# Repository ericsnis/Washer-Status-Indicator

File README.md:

# Washer Status Indicator
Washing Machine status indicator using a ESP32-C3 based Adafruit QT Py

## Features

- Simple LED indicator for at a glance washing machine and clothes dryer status.
  - Green LED for "OFF / Ready"
  - Red LED for "ON/ In Use"
  - Could be used to indicate status of other things.
- Open source hardware
- Software uses [PubSubClient](https://pubsubclient.knolleary.net/) to communicate with MQTT server
  - Uses [OpenHab](https://www.openhab.org/) home automation sever for source of MQTT data.
    - Requires MQTT server such as [Mosquitto](https://mosquitto.org/).
	  - [Basic directions](https://community.openhab.org/t/oh3-mqtt-setup-and-configuration) for Mosquitto and OpenHab
    - Follow directions for configuring [MQTT binding](https://www.openhab.org/addons/bindings/mqtt/).
  - Could be used with other MQTT sources like [Home Assistant](https://www.home-assistant.io/).

## Boards
The schematic folder contains the board and schematic files in Eagle format
- Designs for 1206 SMT LEDs and resistors or through hole components

## Code
The code folder contains the program code to compile and upload to the ESP32
- Use [Platform.io](https://docs.platformio.org/en/latest/integration/ide/vscode.html) installed on [Visual Studio Code](https://code.visualstudio.com/) AKA: VSCode to compile and upload.
- Open the code folder in VSCode then compile, PlatformIO should download any dependencies.

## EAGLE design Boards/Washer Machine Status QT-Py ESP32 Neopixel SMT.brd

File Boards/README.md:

# Boards
 The schematic folder contains the board and schematic files in Eagle format

## Files for surface mount (SMT) boards
- _Washer Machine Status QT-Py ESP32 Neopixel SMT.brd_ - Surface mount board file
- _Washer Machine Status QT-Py ESP32 Neopixel SMT.sch_ - Surface mount schematic file

## Files for through hole component boards
- _Washer Machine Status QT-Py ESP32 Neopixel THT.brd_ - Through hole component board file
- _Washer Machine Status QT-Py ESP32 Neopixel THT.sch_ - Through hole component schematic file

**You need _both_ the .brd and .sch files to open the board in Eagle.**

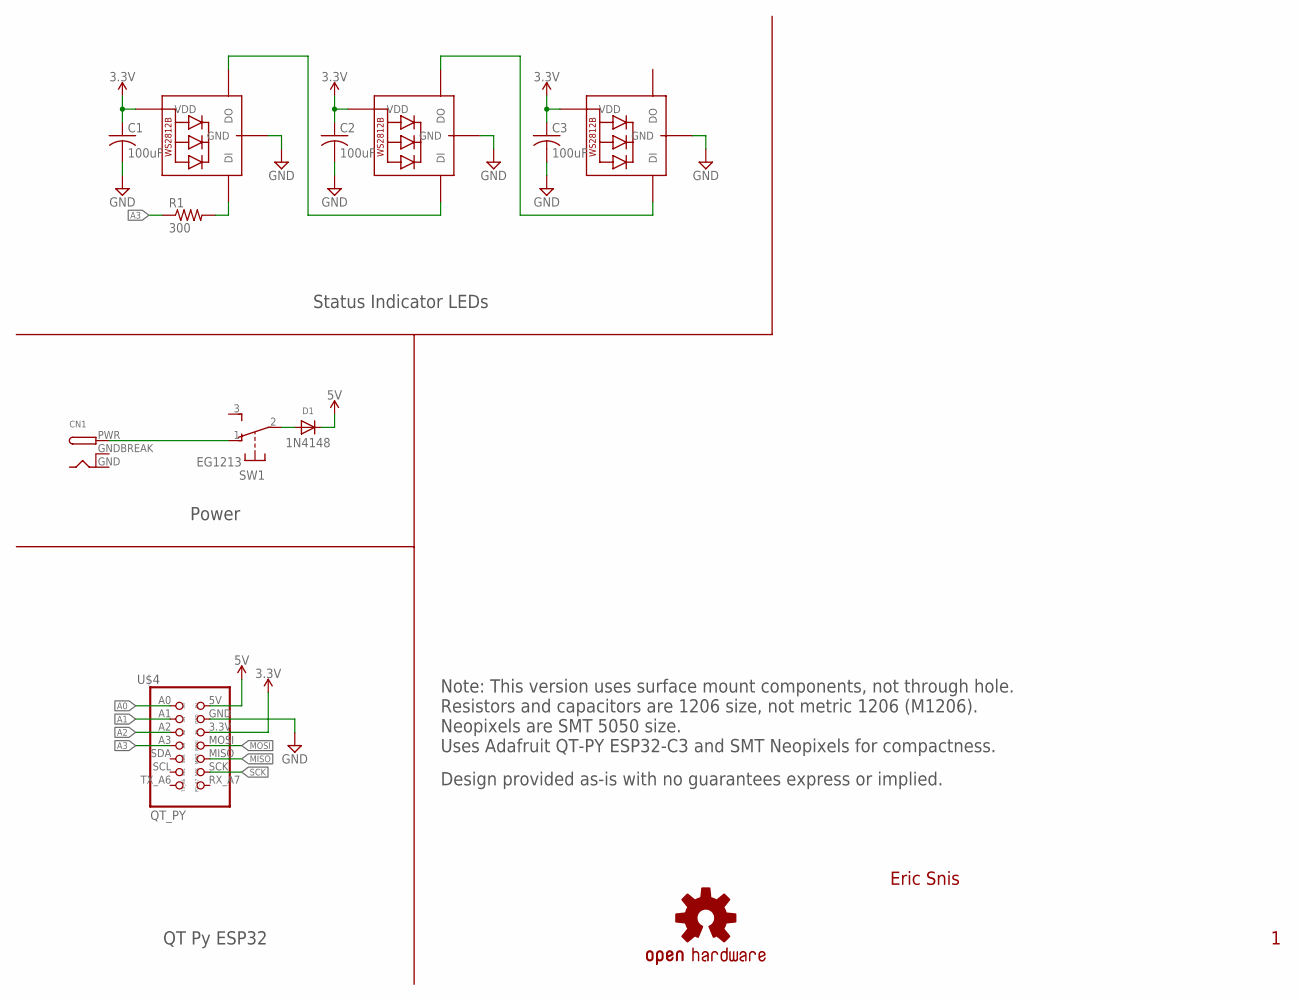
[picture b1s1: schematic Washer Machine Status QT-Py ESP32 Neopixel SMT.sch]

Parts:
C1, C2, C3: 100uF; C1206
CN1: DCBARRELPTH; DCJACK_2MM_PTH
D1: 1N4148; SOD-123FL
LED1, LED2, LED3: WS2812B5050; WS2812B
LOGO2: OSHW-LOGOMINI; OSHW-LOGO-MINI
R1: 300; R1206
SW: EG1213
U$4: QT_PY

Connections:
3.3V: C1.1, C2.1, C3.1, LED1.1-VDD (VDD), LED2.1-VDD (VDD), LED3.1-VDD (VDD), U$4.3.3V (3V)
5V: D1.C, U$4.5V
A0: U$4.A0
A1: U$4.A1
A2: U$4.A2
A3: R1.1, U$4.A3
GND: C1.2, C2.2, C3.2, CN1.GND, LED1.3-GND (GND), LED2.3-GND (GND), LED3.3-GND (GND), U$4.GND
GNDBREAK: CN1.GNDBREAK
MISO: U$4.MISO
MOSI: U$4.MOSI
unnamed: CN1.PWR, SW.1 (O)
unnamed: LED1.2-DOUT (DO), LED2.4-DIN (DI)
unnamed: LED1.4-DIN (DI), R1.2
unnamed: LED2.2-DOUT (DO), LED3.4-DIN (DI)
unnamed: D1.A, SW.2
SCK: U$4.SCK

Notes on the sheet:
Status Indicator LEDs
Power
QT Py ESP32
Note: This version uses surface mount components, not through hole. Resistors and capacitors are 1206 size, not metric 1206 (M1206). Neopixels are SMT 5050 size. Uses Adafruit QT-PY ESP32-C3 and SMT Neopixels for compactness.
Design provided as-is with no guarantees express or implied.

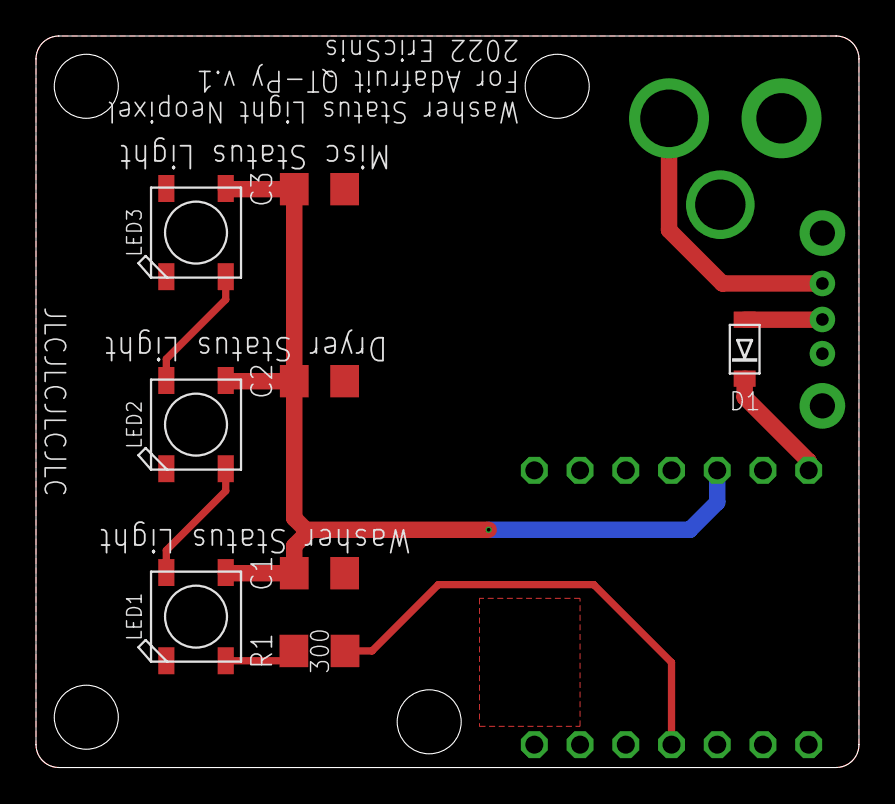
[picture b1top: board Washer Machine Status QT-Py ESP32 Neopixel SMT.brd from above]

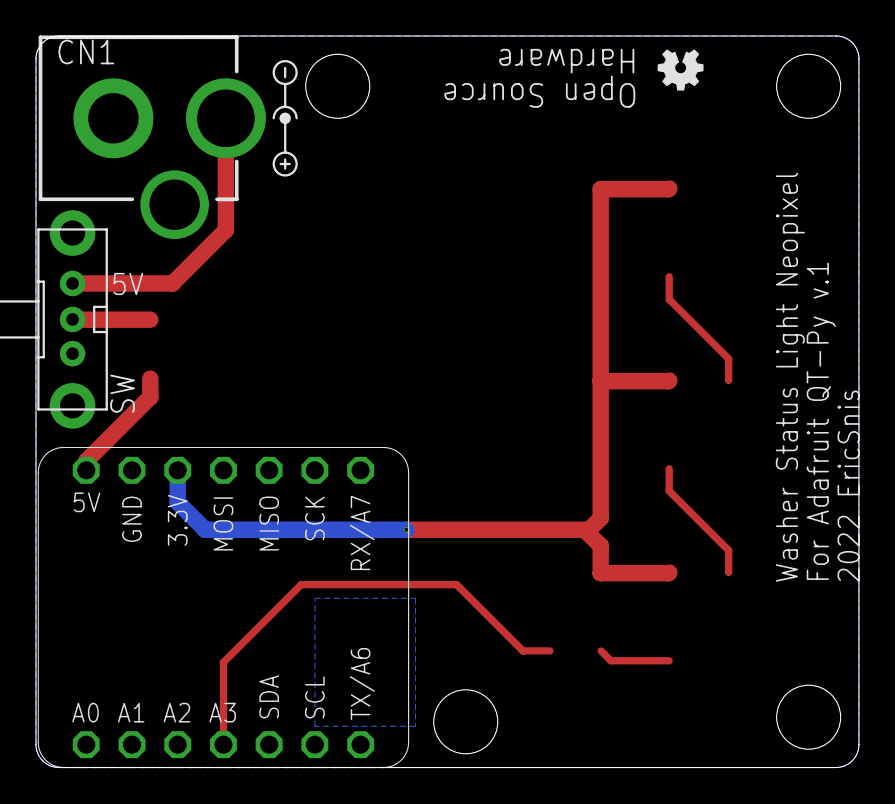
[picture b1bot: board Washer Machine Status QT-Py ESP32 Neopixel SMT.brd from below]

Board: 2 copper layers, 45.7 x 40.6 mm, 13 parts (5 on the bottom side), 9 nets.

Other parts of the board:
U$1: CENTER-POS-SMALL

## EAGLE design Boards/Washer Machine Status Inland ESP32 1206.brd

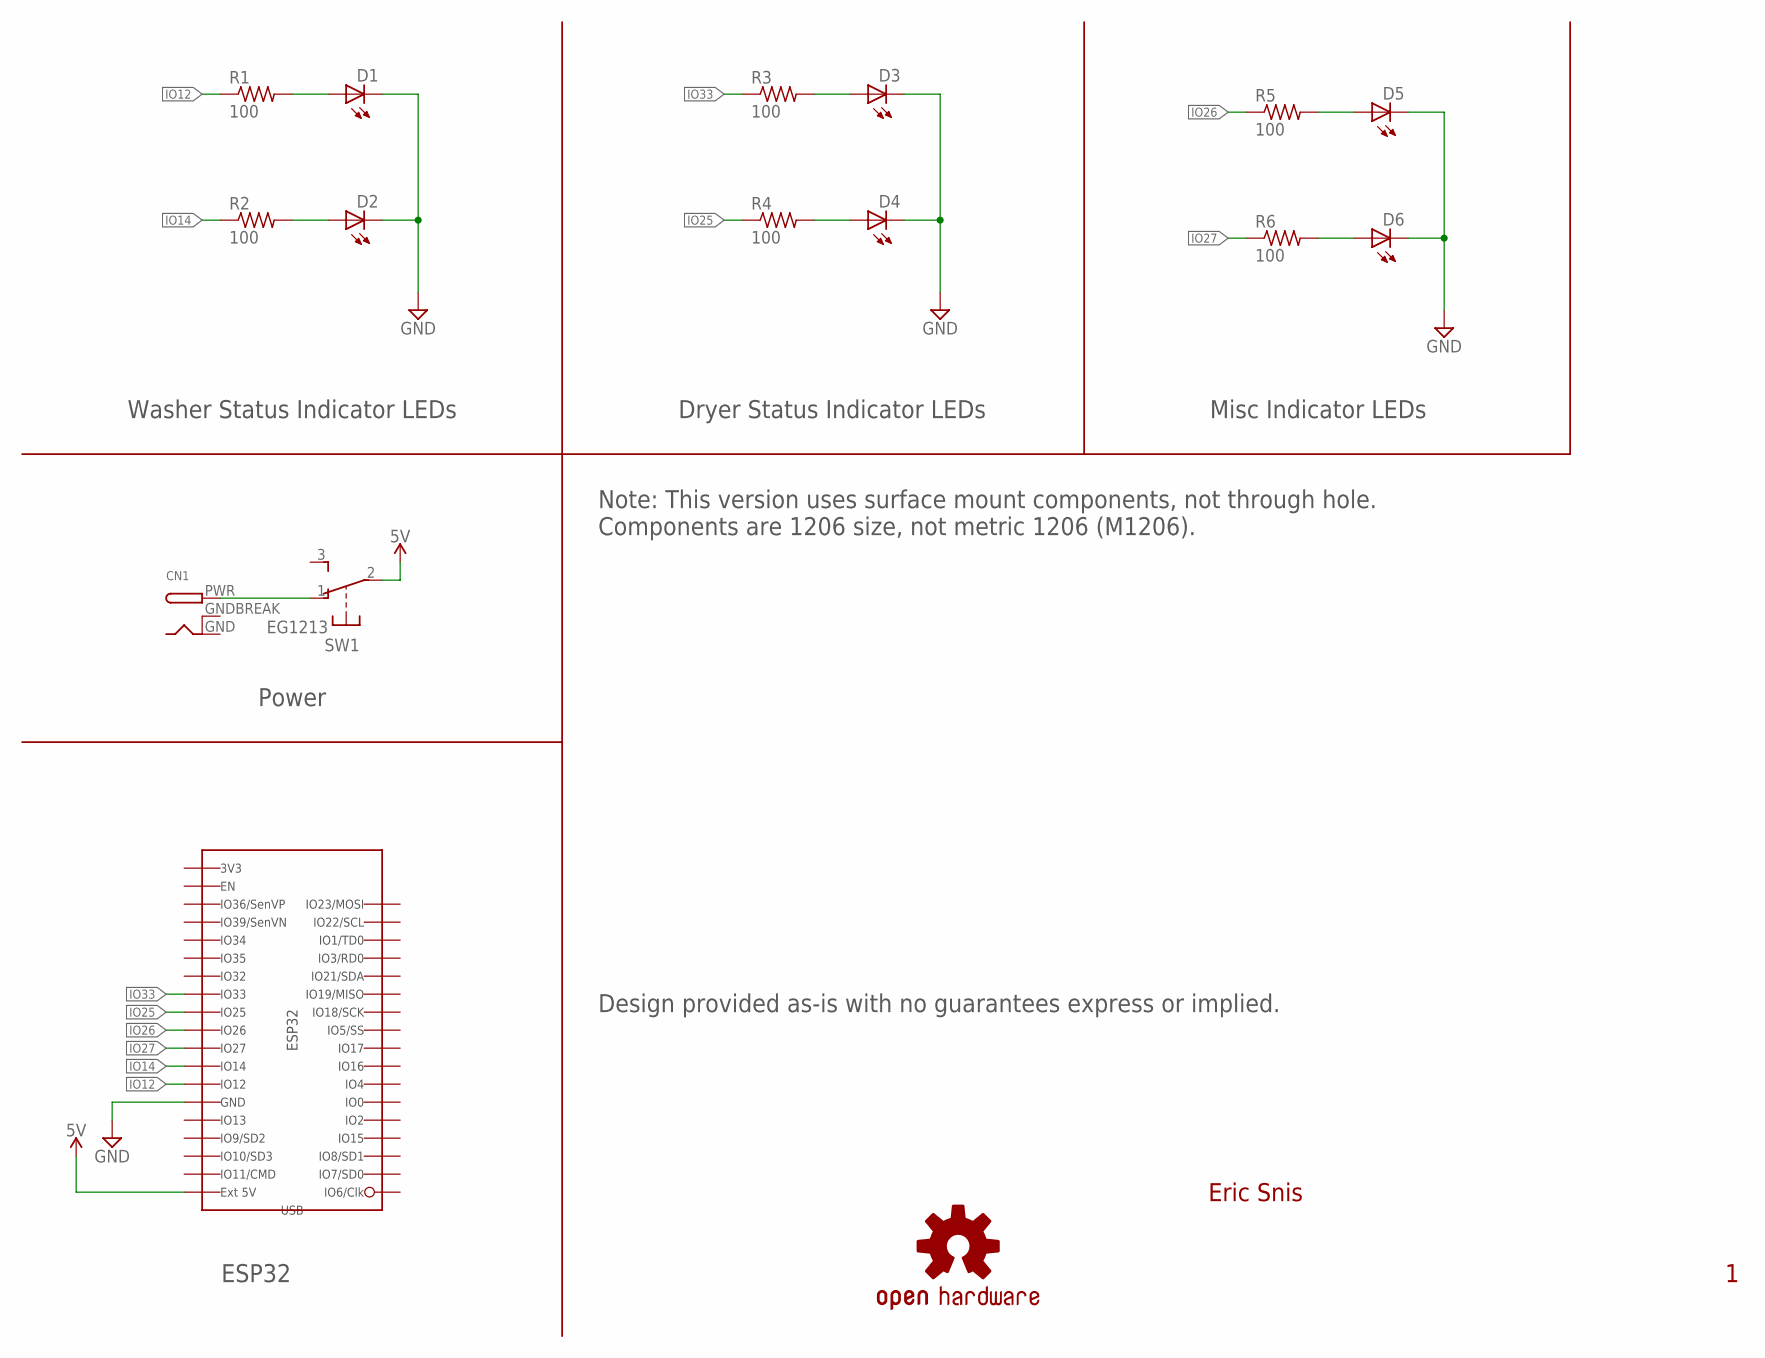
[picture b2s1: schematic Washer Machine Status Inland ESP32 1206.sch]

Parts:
CN1: DCBARRELPTH; DCJACK_2MM_PTH
D1, D3, D5: Green; CHIPLED_1206_LONG
D2, D4, D6: Red; CHIPLED_1206_LONG
LOGO2: OSHW-LOGOMINI; OSHW-LOGO-MINI
R1, R2, R3, R4, R5, R6: 100; R1206
SW: EG1213
U$3: ESP32-INLAND; ESP32_INLAND

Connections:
3V3: U$3.3V3
5V: SW.2, U$3.5V (EXT_5V)
GND: CN1.GND, D1.C, D2.C, D3.C, D4.C, D5.C, D6.C, U$3.GND (GND1), U$3.GND1, U$3.GND2 (GND1)
GNDBREAK: CN1.GNDBREAK
IO12: R1.1, U$3.IO12
IO14: R2.1, U$3.IO14
IO25: R4.1, U$3.IO25
IO26: R5.1, U$3.IO26
IO27: R6.1, U$3.IO27
IO33: R3.1, U$3.IO33
unnamed: CN1.PWR, SW.1 (O)
unnamed: D5.A, R5.2
unnamed: D1.A, R1.2
unnamed: D2.A, R2.2
unnamed: D3.A, R3.2
unnamed: D4.A, R4.2
unnamed: D6.A, R6.2

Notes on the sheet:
Washer Status Indicator LEDs
Power
ESP32
Dryer Status Indicator LEDs
Misc Indicator LEDs
Note: This version uses surface mount components, not through hole. Components are 1206 size, not metric 1206 (M1206).
Design provided as-is with no guarantees express or implied.

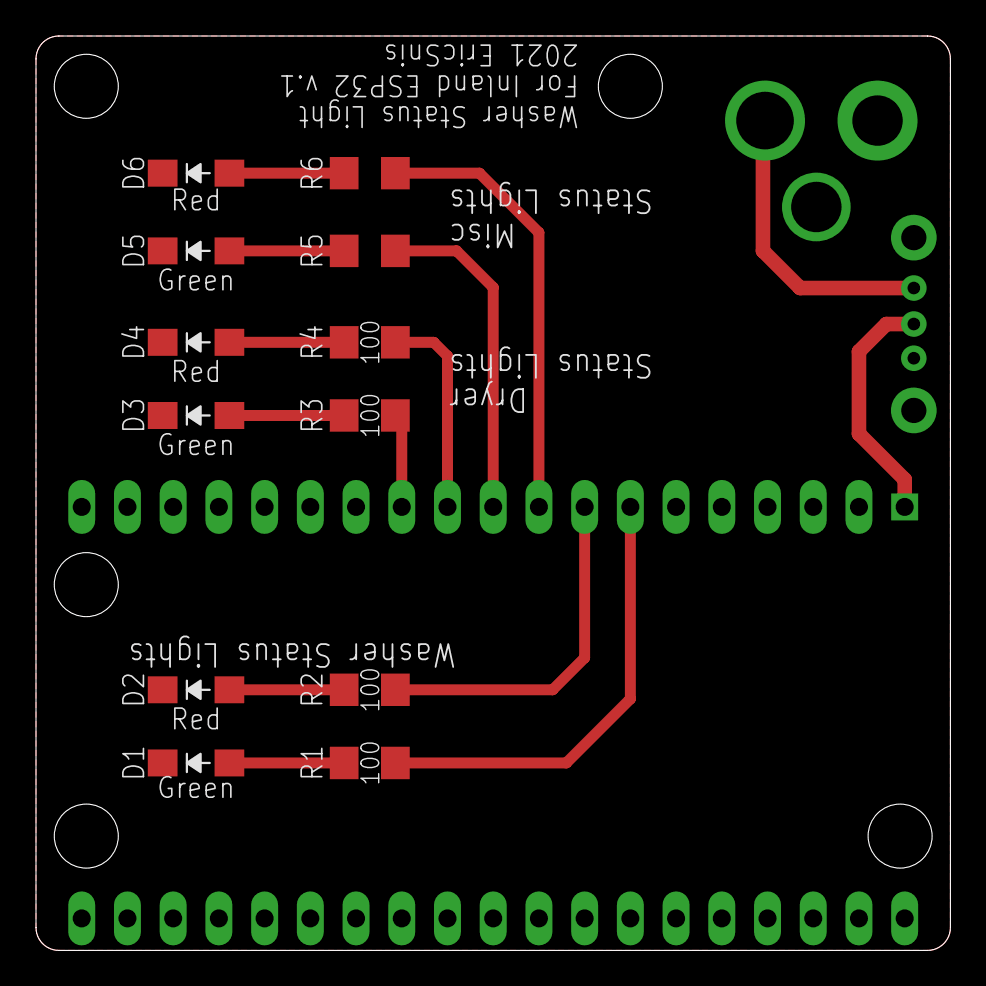
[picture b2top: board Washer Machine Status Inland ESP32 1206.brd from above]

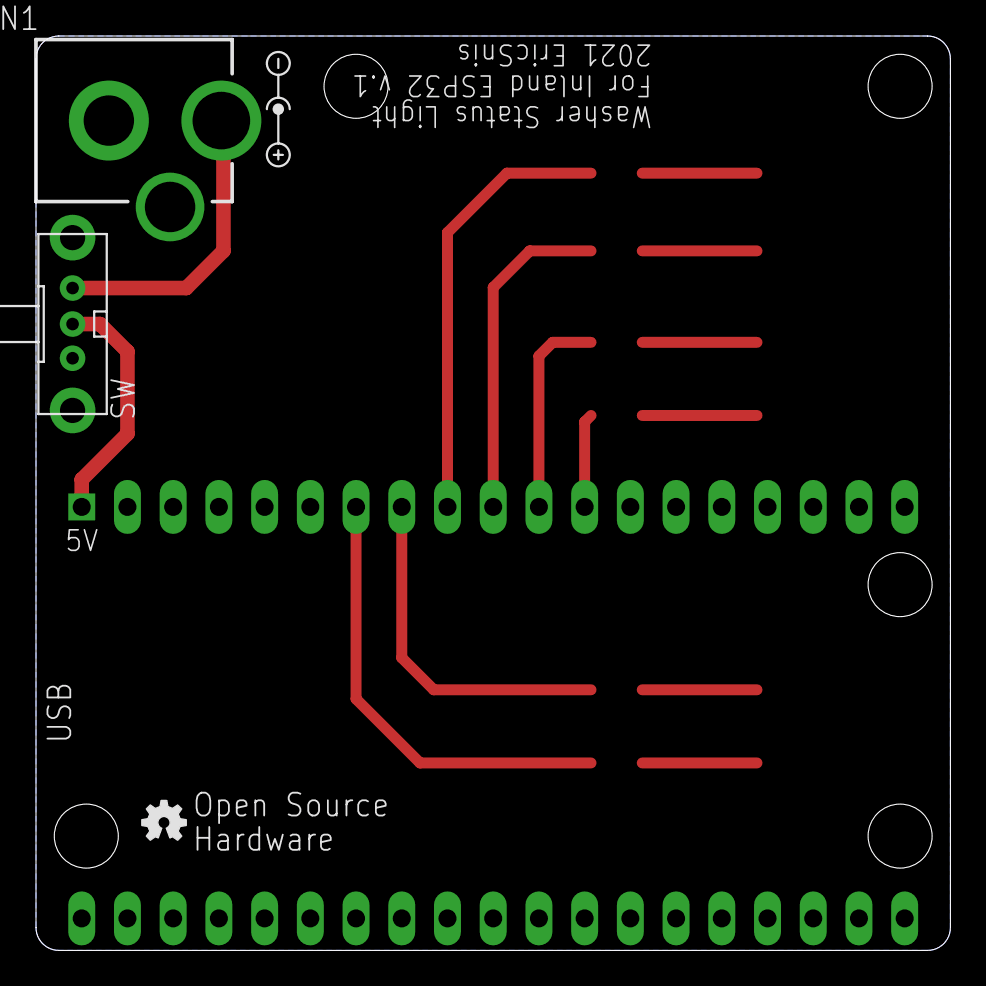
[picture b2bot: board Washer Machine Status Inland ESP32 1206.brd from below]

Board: 2 copper layers, 50.8 x 50.8 mm, 17 parts (5 on the bottom side), 15 nets.

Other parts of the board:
U$1: CENTER-POS-SMALL

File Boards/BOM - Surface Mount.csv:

Qty,Item,Manufacturer,Source,Part #,Website
1,2.1mm DC barrel jack,CUI,Adafruit,373,https://www.adafruit.com/product/373
6,100 Ohm Resistor 1206,Stackpole,DigiKey,RNCP1206FTD100R,https://www.digikey.com/en/products/detail/stackpole-electro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
3,Green LED 1206,Inolux,DigiKey,IN-S126ATG,https://www.digikey.com/en/products/detail/inolux/IN-S126ATG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
3,Red LED 1206,Inolux,DigiKey,IN-S126ATR,https://www.digikey.com/en/products/detail/inolux/IN-S126ATR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
0,Amber LED 1206,Inolux,DigiKey,IN-S126ATA,https://www.digikey.com/en/products/detail/inolux/IN-S126ATA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
1,Slide Switch SPDT Through Hole,E-Switch,DigiKey,EG1213,https://www.digikey.com/en/products/detail/e-switch/EG1213/101735
1,Inland ESP32-WROOM-32D Module,Inland,Microcenter,KS0413,https://www.microcenter.com/product/613822/inland-esp32-wroo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

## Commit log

2023-01-28 initial version

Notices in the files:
parts and their libraries:
SparkFun-Aesthetics: Licensing: Creative Commons ShareAlike 4.0 International - https://creativecommons.org/licenses/by-sa/4.0
